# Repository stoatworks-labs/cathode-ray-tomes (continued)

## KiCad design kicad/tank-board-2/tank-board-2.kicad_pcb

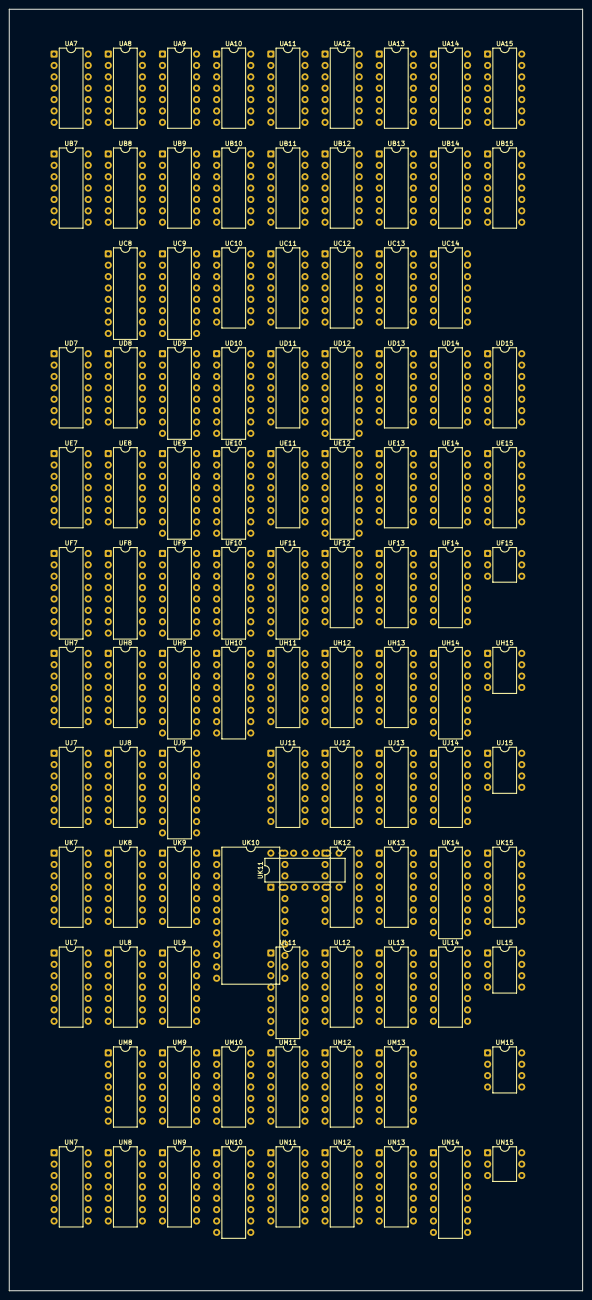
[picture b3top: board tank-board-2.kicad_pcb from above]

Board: 2 copper layers, 128.0 x 286.1 mm, 102 parts (0 on the bottom side), 302 nets, no tracks yet.

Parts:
UA7: 74H04; DIP-14_W7.62mm
UA8, UA15: 7474; DIP-14_W7.62mm
UA9, UA10: 7400; DIP-14_W7.62mm
UA11: 7408; DIP-14_W7.62mm
UA12: 7492; DIP-14_W7.62mm
UA13: 7402; DIP-14_W7.62mm
UA14: 7410; DIP-14_W7.62mm
UB7: 7408; DIP-14_W7.62mm
UB8, UB9, UB11: 7402; DIP-14_W7.62mm
UB10: 7404; DIP-14_W7.62mm
UB12: 7410; DIP-14_W7.62mm
UB13, UB14, UB15: 7400; DIP-14_W7.62mm
UC8, UC9: 9602; DIP-16_W7.62mm
UC10: 7493; DIP-14_W7.62mm
UC11: NE556; DIP-14_W7.62mm
UC12: 74107; DIP-14_W7.62mm
UC13, UC14: 7410; DIP-14_W7.62mm
UD7, UD15: 7402; DIP-14_W7.62mm
UD8: 74107; DIP-14_W7.62mm
UD9: 74153; DIP-16_W7.62mm
UD10: 9322; DIP-16_W7.62mm
UD11: 7493; DIP-14_W7.62mm
UD12: 9316; DIP-16_W7.62mm
UD13: 7420; DIP-14_W7.62mm
UD14: 7400; DIP-14_W7.62mm
UE7: 7420; DIP-14_W7.62mm
UE8: 7486; DIP-14_W7.62mm
UE9: 74153; DIP-16_W7.62mm
UE10: 9322; DIP-16_W7.62mm
UE11: 7493; DIP-14_W7.62mm
UE12: 9316; DIP-16_W7.62mm
UE13: 7404; DIP-14_W7.62mm
UE14: 7400; DIP-14_W7.62mm
UE15: 7402; DIP-14_W7.62mm
UF7: 8277; DIP-16_W7.62mm
UF8, UF10: 9322; DIP-16_W7.62mm
UF9: 74153; DIP-16_W7.62mm
UF11: 74193; DIP-16_W7.62mm
UF12: 7493; DIP-14_W7.62mm
UF13: 7486; DIP-14_W7.62mm
UF14: 7410; DIP-14_W7.62mm
UF15: MFC6040; DIP-6_W7.62mm
UH7: 7474; DIP-14_W7.62mm
UH8: 7400; DIP-14_W7.62mm
UH9: 74153; DIP-16_W7.62mm
UH10: 74193; DIP-16_W7.62mm
UH11: 7408; DIP-14_W7.62mm
UH12: 7493; DIP-14_W7.62mm
UH13: 7410; DIP-14_W7.62mm
UH14: 9316; DIP-16_W7.62mm
UH15: NE566; DIP-8_W7.62mm
UJ7: 7402; DIP-14_W7.62mm
UJ8: 7474; DIP-14_W7.62mm
UJ9: 74153; DIP-16_W7.62mm
UJ11: 7404; DIP-14_W7.62mm
UJ12: 74107; DIP-14_W7.62mm
UJ13: 7400; DIP-14_W7.62mm
UJ14: 7493; DIP-14_W7.62mm
UJ15: NE555; DIP-8_W7.62mm
UK7, UK8: 7400; DIP-14_W7.62mm
UK9, UK12: 7474; DIP-14_W7.62mm
UK10: EA-ROM; DIP-24_W15.24mm
UK11: 7402; DIP-14_W7.62mm
UK13: 7427; DIP-14_W7.62mm
UK14: 9316; DIP-16_W7.62mm
UK15: 7406; DIP-14_W7.62mm
UL7: 7402; DIP-14_W7.62mm
UL8: 7408; DIP-14_W7.62mm
UL9, UL12: 7474; DIP-14_W7.62mm
UL11: 9321; DIP-16_W7.62mm
UL13: 7400; DIP-14_W7.62mm
UL14: 7493; DIP-14_W7.62mm
UL15: NE555; DIP-8_W7.62mm
UM8, UM9, UM11, UM12: 7474; DIP-14_W7.62mm
UM10: 7406; DIP-14_W7.62mm
UM13: 7404; DIP-14_W7.62mm
UM15: NE566; DIP-8_W7.62mm
UN7: 7402; DIP-14_W7.62mm
UN8, UN9, UN11, UN12: 7474; DIP-14_W7.62mm
UN10: 74165; DIP-16_W7.62mm
UN13: 7406; DIP-14_W7.62mm
UN14: 9602; DIP-16_W7.62mm
UN15: MFC6040; DIP-6_W7.62mm

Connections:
+5V: UA7.14, UA8.1, UA8.4, UA8.10, UA8.13, UA8.14, UA9.14, UA10.14, UA11.14, UA12.5, UA13.14, UA14.14, UA15.4, UA15.10, UA15.14, UB7.14, UB8.14, UB9.14, UB10.14, UB11.14, UB12.14, UB13.14, UB14.14, UB15.14, UC8.3, UC8.16, UC9.3, UC9.16, UC10.5, UC11.14, UC12.1, UC12.4, UC12.8, UC12.10, UC12.11, UC12.14, UC13.14, UC14.14, UD7.14, UD8.1, UD8.4, UD8.8, UD8.11, UD8.14, UD9.4, UD9.16, UD10.16, UD11.5, UD12.9, UD12.10, UD12.16, UD13.14, UD14.14, UD15.14, UE7.14, UE8.14, UE9.16, UE10.16, UE11.5, UE12.7, UE12.9, UE12.10, UE12.16, UE13.14, UE14.14, UE15.14, UF7.6, UF7.12, UF7.16, UF8.16, UF9.16, UF10.16, UF11.9, UF11.16, UF12.5, UF13.14, UF14.14, UH7.14, UH8.14, UH9.16, UH10.9, UH10.16, UH11.14, UH12.5, UH13.14, UH14.7, UH14.10, UH14.16, UJ7.14, UJ8.1, UJ8.13, UJ8.14, UJ9.16, UJ11.14, UJ12.1, UJ12.4, UJ12.8, UJ12.11, UJ12.14, UJ13.14, UJ14.5, UJ15.4, UJ15.8, UK7.14, UK8.14, UK9.1, UK9.4, UK9.13, UK9.14, UK10.1, UK10.14, UK10.24, UK11.14, UK12.1, UK12.4, UK12.10, UK12.13, UK12.14, UK13.14, UK14.7, UK14.10, UK14.16, UK15.14, UL7.14, UL8.14, UL9.2, UL9.4, UL9.10, UL9.12, UL9.14, UL11.16, UL12.2, UL12.4, UL12.10, UL12.12, UL12.14, UL13.14, UL14.5, UL15.4, UL15.8, UM8.4, UM8.10, UM8.14, UM9.1, UM9.13, UM9.14, UM10.14, UM11.1, UM11.13, UM11.14, UM12.4, UM12.10, UM12.14, UM13.14, UN7.14, UN8.4, UN8.10, UN8.14, UN9.4, UN9.13, UN9.14, UN10.10, UN10.16, UN11.4, UN11.13, UN11.14, UN12.4, UN12.10, UN12.14, UN13.14, UN14.3, UN14.5, UN14.13, UN14.16
+12V: UF15.4, UH15.8, UM15.8, UN15.4
ACC1: UC14.11, UE15.1
ACC2: UC14.3, UD15.1
ATTRACTQ: UA15.2, UA15.12, UF14.4, UF14.10, UM13.1
BLO_UP1: UC11.5, UN7.3
BLO_UP2: UC11.9, UN7.5
BOUNCE1: UA8.5, UE8.5
BOUNCE1Q: UA8.6, UA9.13, UF14.5, UL13.5
BOUNCE2: UA8.9, UE8.9
BOUNCE2Q: UA8.8, UA9.10, UF14.9, UL13.1
CHECKERBOARD: UD7.2, UF13.6
D0: UF9.10, UF10.4, UJ9.4
D1: UE9.12, UF9.6, UF10.7
D2: UE9.4, UF10.12, UH9.10
D3: UD9.12, UF10.9, UH9.6
D4: UF8.4, UH9.4
D4S: UF8.7, UJ9.10
FIELD: UE7.4, UN10.7
FIRE1: UC9.5, UC9.10
FIRE2: UC8.5, UC8.10
FLASH: UA12.8, UC14.13
G01: UL8.5, UL13.6, UM9.4, UM9.10, UN9.1, UN9.10
G02: UL8.9, UL13.3, UM11.4, UM11.10, UN11.1, UN11.10
GND: UA7.7, UA8.7, UA9.7, UA10.7, UA11.7, UA12.6, UA12.7, UA12.10, UA13.7, UA14.7, UA15.7, UB7.7, UB8.7, UB9.7, UB10.7, UB11.7, UB12.7, UB13.7, UB14.7, UB15.7, UC8.4, UC8.8, UC8.12, UC9.4, UC9.8, UC9.12, UC10.10, UC11.7, UC12.7, UC13.7, UC14.7, UD7.7, UD8.7, UD9.1, UD9.5, UD9.8, UD9.15, UD10.8, UD10.15, UD11.10, UD12.8, UD13.7, UD14.7, UD15.7, UE7.7, UE8.7, UE9.1, UE9.8, UE9.15, UE10.8, UE10.10, UE10.11, UE10.13, UE10.14, UE10.15, UE11.10, UE12.8, UE13.7, UE14.7, UE15.7, UF7.5, UF7.7, UF7.8, UF7.10, UF7.11, UF8.8, UF8.15, UF9.1, UF9.8, UF9.15, UF10.8, UF10.15, UF11.1, UF11.8, UF11.10, UF11.14, UF11.15, UF12.10, UF13.7, UF14.7, UH7.2, UH7.7, UH7.12, UH8.7, UH9.1, UH9.8, UH9.15, UH10.1, UH10.8, UH10.10, UH10.14, UH10.15, UH11.7, UH12.10, UH13.7, UH14.3, UH14.8, UH15.1, UJ7.7, UJ8.2, UJ8.7, UJ8.12, UJ9.1, UJ9.6, UJ9.8, UJ9.15, UJ11.7, UJ12.7, UJ13.7, UJ14.10, UJ15.1, UK7.7, UK8.7, UK9.7, UK9.12, UK11.7, UK12.7, UK13.7, UK14.3, UK14.8, UK15.7, UL7.7, UL8.7, UL9.7, UL11.8, UL12.7, UL13.7, UL14.10, UL15.1, UM8.7, UM9.7, UM10.7, UM11.7, UM12.7, UM13.7, UM15.1, UN7.7, UN8.7, UN9.7, UN10.8, UN10.15, UN11.7, UN12.7, UN13.7, UN14.8, UN14.12
H2: UB12.13, UD13.2, UE12.13, UF13.13
H4: UE12.12, UE13.9, UF13.12
H4Q: UE13.8, UN10.2
H8: UA10.12, UB11.3, UE12.11
H16: UB11.2, UC13.11, UD12.14, UD13.12, UD14.5, UE13.11, UK10.13
H32: UC13.3, UD12.13, UD13.13, UE13.13, UL11.2
H32Q: UB14.1, UE13.12, UJ9.12
H64: UD12.12, UD13.5, UE13.5, UF8.1, UF9.13, UF10.1, UH8.2, UL11.3
H64Q: UA14.9, UE13.6, UH8.12
H128: UA13.12, UC13.4, UC13.10, UC13.13, UD12.11, UD13.4, UD13.9, UF9.3
H256: UA11.2, UC12.3, UC12.9, UC13.2, UD13.1, UH9.13
H452: UA11.1, UC12.5, UC13.9, UH9.3
H452Q: UB12.5, UC12.6, UC13.1, UC13.5, UD10.1, UE10.1, UF14.2, UK9.3
HIT1: UB8.5, UJ7.12, UJ8.9
HIT1Q: UH11.2, UJ8.8
HIT2: UB9.5, UJ7.2, UJ8.5
HIT2Q: UH11.5, UJ8.6
HMCEQ: UA15.3, UA15.11, UK9.5, UK9.10
HT1Q: UB10.5, UC11.4, UC11.6, UD11.1, UJ7.13
HT2Q: UB10.3, UC10.14, UC11.8, UC11.10, UJ7.1
H_BLANK: UB12.4, UB14.2, UB14.6, UF12.14
H_COUNTQ: UB12.12, UL8.4, UL8.10
H_INFO: UA13.9, UA13.13, UA14.11, UD14.4
H_INFOQ: UA10.10, UA13.10, UA13.11, UD9.14, UE8.13, UE9.14, UF9.14, UH9.14, UJ9.14, UL9.11
H_RESET: UK12.6, UK12.11
H_RESETQ: UB12.3, UB14.5, UC12.13, UD12.1, UE12.1, UK12.5
H_SYNC: UA11.13, UA13.8, UB12.1, UE13.4
H_SYNCQ: UA14.10, UB12.6, UE13.3
LDH1BQ: UK11.6, UL11.5
LDH2BQ: UK11.3, UL11.7
MEH: UB13.3, UB13.4
MEHQ: UA13.6, UB13.1, UB13.6
MEV: UA11.10, UB14.8, UB14.12
MEVQ: UA13.5, UB14.10, UB14.11
MINE: UD7.11, UE7.8, UK7.2, UK7.12
MINEFIELD: UA13.4, UE7.1, UK13.1
MINE_MATRIX: UD7.1, UE7.2
MTK1: UH7.5, UJ7.11, UL7.5
MTK1Q: UH7.6, UK7.10
MTK2: UH7.9, UJ7.3, UL7.9
MTK2Q: UH7.8, UK7.9
unnamed: UA7.1, UA7.3, UA7.12
unnamed: UC11.12, UC11.13
unnamed: UC11.1, UC11.2
unnamed: UD15.5, UD15.11
unnamed: UD15.6, UD15.9
unnamed: UD15.3, UD15.8
unnamed: UD15.2, UD15.12
unnamed: UE15.5, UE15.11
unnamed: UE15.6, UE15.9
unnamed: UE15.3, UE15.8
unnamed: UE15.2, UE15.12
unnamed: UD9.3, UD9.6
unnamed: UK10.16, UM10.9
unnamed: UK10.17, UM10.5
unnamed: UK10.18, UM10.11
unnamed: UK10.19, UM10.13
unnamed: UK10.20, UM10.1
unnamed: UK10.21, UM10.3
unnamed: UK10.22, UN13.11
unnamed: UK10.23, UN13.9
unnamed: UA7.2, UD12.2, UE12.2, UK12.3
unnamed: UA8.2, UA9.3, UA9.12
unnamed: UA8.12, UA9.6, UA9.9
unnamed: UA9.1, UB9.1
unnamed: UA9.4, UB8.1
unnamed: UA9.5, UA9.8
unnamed: UA9.2, UA9.11
unnamed: UA10.3, UA10.4
unnamed: UA10.5, UH13.12
unnamed: UA10.6, UA10.9
unnamed: UA11.5, UC14.12
unnamed: UA11.8, UF7.9, UH7.3, UH7.11
unnamed: UA11.11, UH13.9
unnamed: UA12.1, UA12.12, UB12.10
unnamed: UA12.11, UB12.9
unnamed: UA13.2, UM13.2, UN13.1, UN13.13
unnamed: UA13.3, UB12.8
unnamed: UA14.3, UA14.4, UA14.5, UA14.8
unnamed: UA14.6, UB11.5
unnamed: UA15.1, UN7.4
unnamed: UA15.5, UB15.13
unnamed: UA15.9, UB15.10
unnamed: UA15.13, UN7.1
unnamed: UB7.3, UB8.6
unnamed: UB7.6, UB9.6
unnamed: UB7.9, UN7.10
unnamed: UB7.10, UD7.13
unnamed: UB8.4, UC8.13
unnamed: UB8.10, UB8.12
unnamed: UB8.3, UB8.13
unnamed: UB9.4, UC9.13
unnamed: UB9.10, UB9.11
unnamed: UB9.3, UB9.13
unnamed: UB8.2, UB10.4
unnamed: UB9.2, UB10.6
unnamed: UB11.1, UB12.2
unnamed: UB11.9, UB11.13
unnamed: UB13.2, UC13.12
unnamed: UB13.5, UC13.8
unnamed: UB13.9, UD13.8
unnamed: UB13.10, UB13.11, UE14.5
unnamed: UB13.12, UC13.6
unnamed: UB13.8, UB13.13
unnamed: UB14.3, UB14.4
unnamed: UB14.9, UH13.6
unnamed: UB14.13, UH13.8
unnamed: UB15.5, UB15.8, UC8.11
unnamed: UB15.6, UB15.9
unnamed: UB15.2, UB15.11, UC9.11
unnamed: UB15.3, UB15.12
unnamed: UC12.12, UD12.15
unnamed: UC14.5, UL13.11
unnamed: UC14.6, UL14.1
unnamed: UC14.8, UJ14.1
unnamed: UC14.9, UL13.8
unnamed: UD8.9, UH11.11
unnamed: UD8.12, UH11.8
unnamed: UD9.7, UK10.8
unnamed: UD9.9, UK10.10
unnamed: UD12.7, UE12.15
unnamed: UD13.6, UK12.2
unnamed: UD14.3, UF14.11
unnamed: UD14.6, UL11.1
unnamed: UD14.8, UF11.4
unnamed: UD14.11, UH11.1
unnamed: UE7.5, UF7.4, UJ7.10
unnamed: UE7.6, UE7.9, UE7.10, UE7.12, UE7.13
unnamed: UE8.11, UK10.15
unnamed: UE9.7, UK10.11
unnamed: UE9.9, UK10.12
unnamed: UE14.3, UF14.3
unnamed: UE14.8, UH10.4
unnamed: UE14.11, UH11.4
unnamed: UF7.3, UF7.13
unnamed: UF7.14, UJ7.9
unnamed: UF9.7, UK10.3
unnamed: UF9.9, UK10.2
unnamed: UF11.5, UH11.3
unnamed: UF11.12, UH11.12
unnamed: UF11.13, UH11.13
unnamed: UF13.5, UF13.8
unnamed: UF13.4, UF13.11
unnamed: UF14.6, UJ14.2, UJ14.3
unnamed: UF14.8, UL14.2, UL14.3
unnamed: UH7.4, UK7.11
unnamed: UH7.10, UK7.3
unnamed: UH8.3, UH8.9
unnamed: UH8.4, UJ11.8
unnamed: UH8.5, UL7.13
unnamed: UH8.10, UH8.11
unnamed: UH9.7, UK10.5
unnamed: UH9.9, UK10.4
unnamed: UH10.5, UH11.6
unnamed: UH10.12, UH11.10
unnamed: UH10.13, UH11.9
unnamed: UH14.1, UM13.6
unnamed: UH14.9, UL13.4, UM13.10
unnamed: UH14.15, UM13.11
unnamed: UJ7.8, UK7.8
unnamed: UJ8.4, UK8.6
unnamed: UJ8.10, UK8.8
unnamed: UJ9.7, UK10.7
unnamed: UJ9.9, UK10.6
unnamed: UJ11.3, UK11.9, UK11.13
unnamed: UJ11.4, UK11.2, UK11.5
unnamed: UJ13.6, UK12.12
unnamed: UJ13.8, UJ13.12
unnamed: UK7.4, UL7.4
unnamed: UK7.5, UL7.10
unnamed: UK7.6, UN14.4
unnamed: UK8.3, UL8.2
unnamed: UK8.11, UL8.12
unnamed: UK9.2, UK9.9
unnamed: UK11.10, UK11.11
unnamed: UK13.2, UN10.9
unnamed: UK13.6, UM13.9
unnamed: UK13.8, UM13.5
unnamed: UK14.1, UM13.8
unnamed: UK14.9, UL13.2, UM13.12
unnamed: UK14.15, UM13.13
unnamed: UL7.1, UN14.11
unnamed: UL8.6, UM8.1, UM8.13, UN8.1, UN8.13
unnamed: UL8.8, UM12.1, UM12.13, UN12.1, UN12.13
unnamed: UL8.11, UL9.1, UL9.13
unnamed: UL8.3, UL12.1, UL12.13
unnamed: UN13.3, UN14.10
unnamed: UN13.5, UN14.6
OOB: UE14.6, UK8.1, UK8.12
P1D0: UF10.2, UH10.3
P1D1: UF10.5, UH10.2
P1D2: UF10.14, UH10.6
P1D3: UF10.11, UH10.7
P1D4: UD8.2, UE8.4, UF8.2
P1D4S: UE8.6, UF8.5
P1SP0: UH14.4, UJ14.9, UK13.9, UK15.9
P1SP1: UH14.5, UJ14.8, UK13.10, UK15.11, UL13.9
P1SP2: UH14.6, UJ14.11, UK13.11, UK15.13, UL13.10
P2D0: UF10.3, UF11.3
P2D1: UF10.6, UF11.2
P2D2: UF10.13, UF11.6
P2D3: UF10.10, UF11.7
P2D4: UD8.5, UE8.10, UF8.3
P2D4S: UE8.8, UF8.6
P2SP0: UK13.4, UK14.4, UK15.5, UL14.9
P2SP1: UK13.5, UK14.5, UK15.3, UL13.12, UL14.8
P2SP2: UK13.3, UK14.6, UK15.1, UL13.13, UL14.11
PFLDQ: UA10.8, UN10.1
PLAYFIELD: UA11.4, UB7.1, UB7.4, UB8.8, UB9.8, UK13.12
PLAYFIELD_VIDEO: UA11.6, UF14.13, UJ11.9
RESET2: UA11.3, UD13.10, UL12.3
RL1: UE14.10, UE15.13
RL2: UD14.10, UD15.13
ROM_D0: UM8.12, UM12.12, UN10.11, UN13.8
ROM_D1: UM8.2, UM12.2, UN10.12, UN13.10
ROM_D2: UM10.4, UN8.12, UN10.13, UN12.12
ROM_D3: UM10.2, UN8.2, UN10.14, UN12.2
ROM_D4: UM9.12, UM10.12, UM11.12, UN10.3
ROM_D5: UM9.2, UM10.10, UM11.2, UN10.4
ROM_D6: UM10.6, UN9.12, UN10.5, UN11.12
ROM_D7: UM10.8, UN9.2, UN10.6, UN11.2
RR1: UE14.13, UE15.10
RR2: UD14.13, UD15.10
SCR1A: UC10.1, UC10.12, UD10.2
SCR1B: UC10.9, UD10.5
SCR1C: UC10.8, UD10.14
SCR1D: UC10.11, UD10.11, UD11.14
SCR1E: UD11.12, UE10.2, UE11.14
SCR1F: UE10.5, UE11.12
SCR2A: UD10.3, UD11.9
SCR2B: UD10.6, UD11.8
SCR2C: UD10.13, UD11.11, UE11.1
SCR2D: UD10.10, UE11.9
SCR2E: UE10.3, UE11.8
SCR2F: UE10.6, UE11.11
SCRA: UD10.4, UH9.5
SCRB: UD10.7, UJ9.11
SCRC: UD10.12, UJ9.5
SCRD: UD10.9, UE9.11
SCRE: UE9.5, UE10.4
SCRF: UD9.11, UE10.7
SHELL1: UB7.5, UK8.5, UL7.11
SHELL2: UB7.2, UK8.9, UN7.8
SQUARES: UA10.11, UD7.3
START: UC10.2, UC10.3, UD11.2, UD11.3, UE11.2, UE11.3, UM13.3
STARTQ: UD8.10, UD8.13, UF7.1, UF11.11, UH7.1, UH7.13, UH10.11, UL8.1, UL8.13, UM13.4
STOP1: UE14.1, UE15.4
STOP2: UD14.1, UD15.4
T2: UF8.12, UF9.12
T3: UF8.9, UF9.4
T4: UH8.8, UH9.12
TANK1: UB8.9, UB10.9, UK7.13, UK8.10, UK8.13
TANK1Q: UB9.12, UB10.1, UB10.8
TANK2: UB9.9, UB10.11, UD7.12, UK7.1, UK8.2, UK8.4
TANK2Q: UB8.11, UB10.10
TM1: UA13.1, UC14.4, UC14.10, UD14.2, UD14.9, UD14.12, UE14.2, UE14.9, UE14.12
V1: UF12.1, UF12.12
V2: UF12.9, UF13.9, UK11.12
V4: UF9.11, UF12.8, UF13.10
V8: UA10.13, UA11.9, UB11.8, UF9.5, UF12.11, UH12.14, UJ13.5
V16: UH9.11, UH12.1, UH12.12, UJ9.13, UJ13.9
V32: UH12.9, UH13.2, UH13.3, UH13.11, UJ9.3
V64: UE9.10, UE9.13, UH12.8, UJ13.10
V128: UE9.3, UE9.6, UH12.11, UH13.4, UH13.10, UJ12.12
V256: UA11.12, UD9.10, UD9.13, UJ12.3, UJ12.9, UL12.11
V256Q: UH13.5, UJ12.2
V512: UJ12.5, UJ13.4, UK13.13
V512Q: UJ12.6, UJ13.2
VLD1: UH14.2, UJ11.5, UK11.4
VLD1Q: UJ11.6, UM8.3, UM8.11, UM9.3, UM9.11, UN8.3, UN8.11, UN9.3, UN9.11
VLD2: UB12.11, UJ11.1, UK9.11, UK11.1, UK14.2
VLD2Q: UJ11.2, UM11.3, UM11.11, UM12.3, UM12.11, UN11.3, UN11.11, UN12.3, UN12.11
V_INFO: UC14.1, UF14.1, UH13.1, UJ13.3, UJ13.13
V_INFOQ: UA10.2, UD9.2, UE8.12, UE9.2, UE14.4, UF9.2, UH9.2, UJ9.2, UJ13.1, UJ13.11
V_RESET: UA8.3, UA8.11, UB11.12, UF12.2, UF12.3, UH12.2, UH12.3, UJ8.3, UJ8.11, UK11.8, UK12.8, UL9.3
V_RESETQ: UA12.14, UJ12.10, UJ12.13, UK12.9
V_SYNC: UB11.6, UB11.10, UB11.11
